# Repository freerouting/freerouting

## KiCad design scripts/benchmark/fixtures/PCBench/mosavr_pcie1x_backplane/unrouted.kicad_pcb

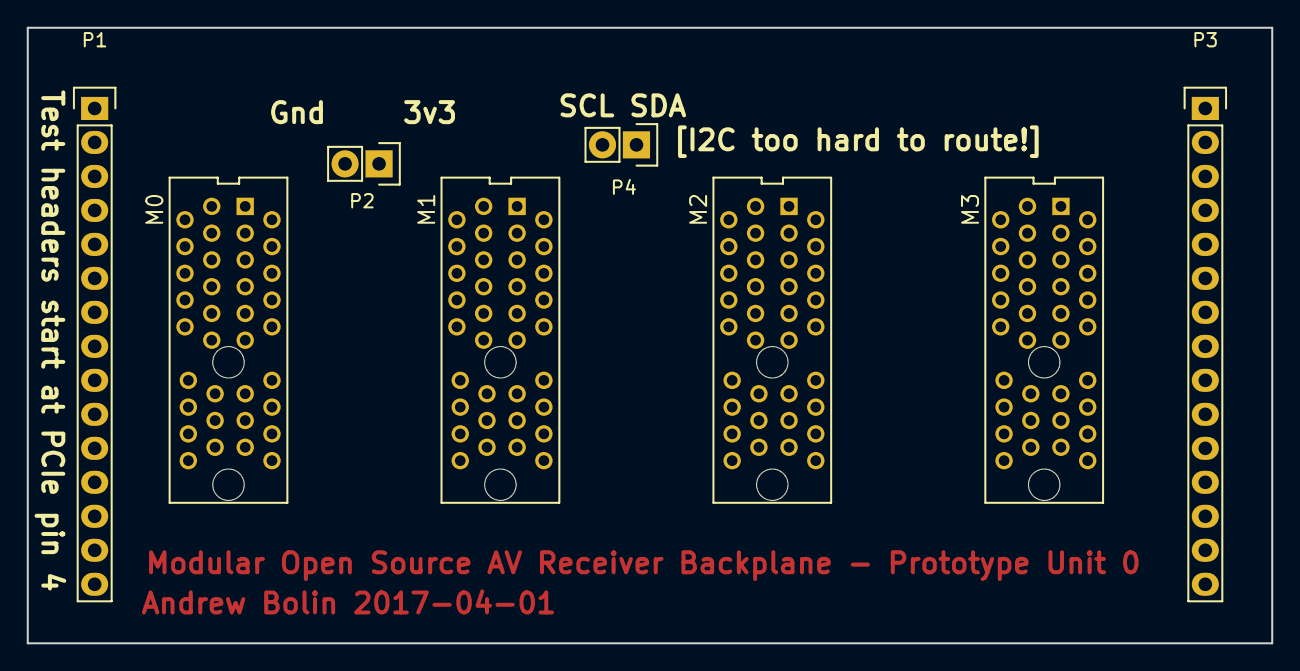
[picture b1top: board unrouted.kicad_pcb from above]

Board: 2 copper layers, 93.0 x 46.0 mm, 8 parts (0 on the bottom side), 54 nets, no tracks yet.

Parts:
M0, M1, M2, M3: pcie_1x_conn; x1socket
P1, P3: CONN_01X15; Pin_Header_Straight_1x15
P2, P4: CONN_01X02; Pin_Header_Straight_1x02

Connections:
+3V3: M0.A5, M0.A17, M0.B5, M0.B17, M1.A5, M1.A17, M1.B1, M1.B5, M1.B17, M2.A5, M2.A17, M2.B2, M2.B5, M2.B17, M3.A5, M3.A17, M3.B1, M3.B2, M3.B5, M3.B17, P1.2, P1.14, P2.1, P3.2, P3.14
/SCL: M0.B7, M1.B7, M2.B7, M3.B7, P1.4, P4.2
/SDA: M0.A7, M1.A7, M2.A7, M3.A7, P3.4, P4.1
GND: M0.A4, M0.A16, M0.B1, M0.B2, M0.B3, M0.B4, M0.B16, M1.A4, M1.A16, M1.B4, M1.B16, M2.A4, M2.A16, M2.B1, M2.B3, M2.B4, M2.B16, M3.A4, M3.A16, M3.B3, M3.B4, M3.B16, P1.1, P1.13, P2.2, P3.1, P3.13
unnamed: M0.A6, M1.B6
unnamed: M0.A8, M1.B8
unnamed: M0.A9, M1.B9
unnamed: M0.A10, M1.B10
unnamed: M0.A11, M1.B11
unnamed: M0.A12, M1.B12
unnamed: M0.A13, M1.B13
unnamed: M0.A14, M1.B14
unnamed: M0.A15, M1.B15
unnamed: M0.A18, M1.B18
unnamed: M0.B6, P1.3
unnamed: M0.B8, P1.5
unnamed: M0.B9, P1.6
unnamed: M0.B10, P1.7
unnamed: M0.B11, P1.8
unnamed: M0.B12, P1.9
unnamed: M0.B13, P1.10
unnamed: M0.B14, P1.11
unnamed: M0.B15, P1.12
unnamed: M0.B18, P1.15
unnamed: M1.A6, M2.B6
unnamed: M1.A8, M2.B8
unnamed: M1.A9, M2.B9
unnamed: M1.A10, M2.B10
unnamed: M1.A11, M2.B11
unnamed: M1.A12, M2.B12
unnamed: M1.A13, M2.B13
unnamed: M1.A14, M2.B14
unnamed: M1.A15, M2.B15
unnamed: M1.A18, M2.B18
unnamed: M2.A6, M3.B6
unnamed: M2.A8, M3.B8
unnamed: M2.A9, M3.B9
unnamed: M2.A10, M3.B10
unnamed: M2.A11, M3.B11
unnamed: M2.A12, M3.B12
unnamed: M2.A13, M3.B13
unnamed: M2.A14, M3.B14
unnamed: M2.A15, M3.B15
unnamed: M2.A18, M3.B18
unnamed: M3.A6, P3.3
unnamed: M3.A8, P3.5
unnamed: M3.A9, P3.6
unnamed: M3.A10, P3.7
unnamed: M3.A11, P3.8
unnamed: M3.A12, P3.9
unnamed: M3.A13, P3.10
unnamed: M3.A14, P3.11
unnamed: M3.A15, P3.12
unnamed: M3.A18, P3.15

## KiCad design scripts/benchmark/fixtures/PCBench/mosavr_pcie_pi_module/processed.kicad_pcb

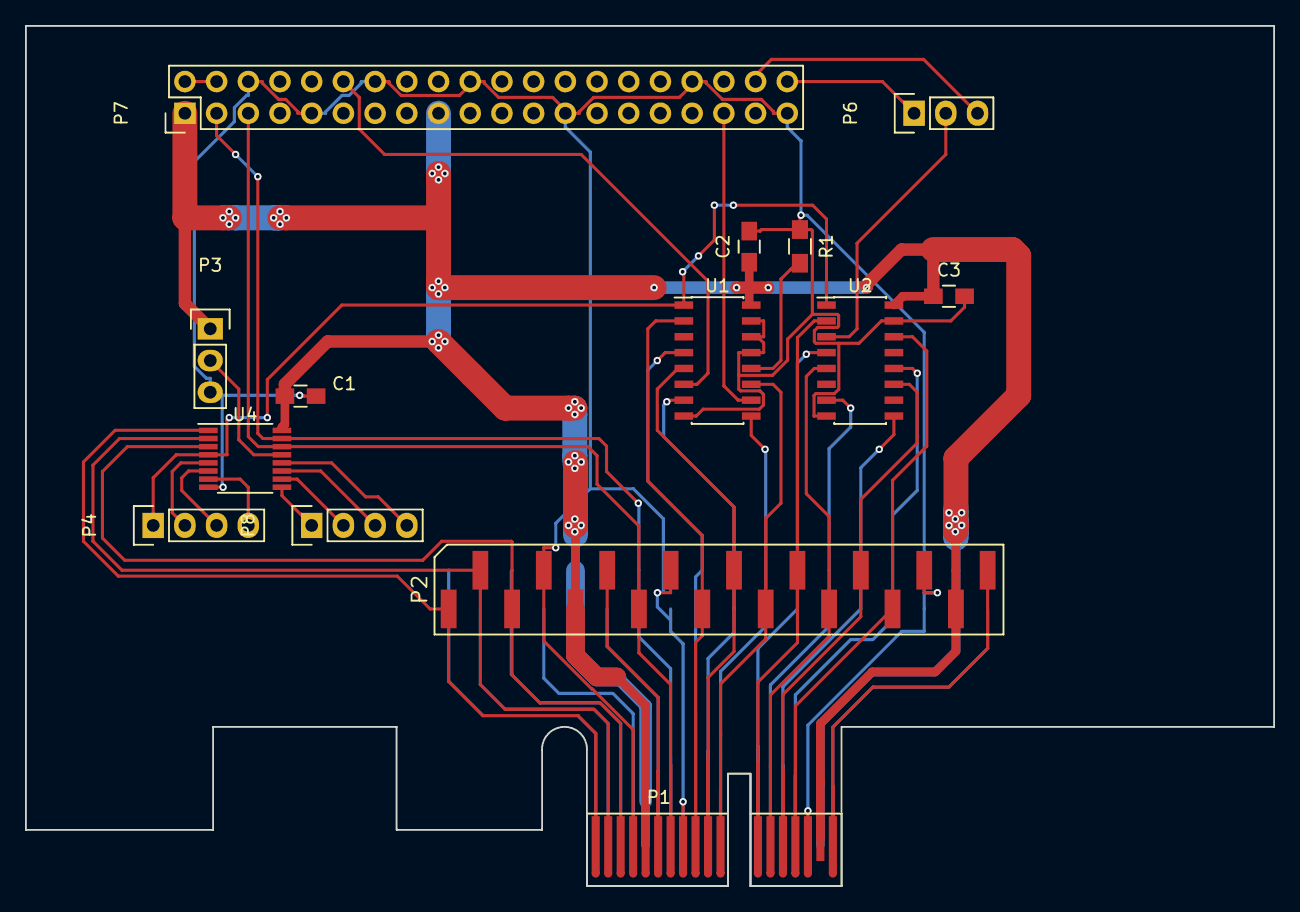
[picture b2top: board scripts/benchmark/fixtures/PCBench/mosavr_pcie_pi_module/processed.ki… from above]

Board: 2 copper layers, 100.0 x 68.9 mm, 15 parts (1 on the bottom side), 45 nets.

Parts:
C1, C2, C3: 0.1uF; C_0805_HandSoldering
P1: pcie_1x_edge; PCI-EXPRESS
P2, P5: CONN_01X18; smd_1x18_B
P3, P6: CONN_01X03; Pin_Header_Straight_1x03
P4, P8: CONN_01X04; Pin_Header_Straight_1x04
P7: CONN_02X20; Pin_Header_Straight_2x20
R1: 10k; R_0805_HandSoldering
U1, U2: 74HCT157; SOIC-16_3.9x9.9mm_Pitch1.27mm
U4: PCA9500; TSSOP-16_4.4x5mm_Pitch0.65mm

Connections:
+3V3: C1.1, C2.1, C3.1, P1.A5, P1.A17, P1.B5, P1.B17, P2.5, P2.17, P3.1, P5.5, P5.17, P7.1, P7.17, U1.16, U2.16, U4.16
+5V: P7.2, P7.4
/A0: P1.B1, P2.1, U4.1
/A1: P1.B2, P2.2, U4.2
/A2: P1.B3, P2.3, U4.3
/I2S0_in: P1.B12, P2.12, U2.2
/I2S0_mod: P6.2, U2.3
/I2S0_out: P1.A12, P5.12, U2.4
/I2S1_in: P1.B13, P2.13, U2.5
/I2S1_out: P1.A13, P5.13, U2.7
/I2S2_in: P1.B14, P2.14, U2.11
/I2S2_out: P1.A14, P5.14, U2.9
/I2S3_in: P1.B15, P2.15, U2.14
/I2S3_out: P1.A15, P5.15, U2.12
/LRclk_in: P1.B11, P2.11, U1.11
/LRclk_mod: P7.35, U1.10
/LRclk_out: P1.A11, P5.11, U1.9
/Mclk_in: P1.B9, P2.9, U1.2
/Mclk_out: P1.A9, P5.9, U1.4
/SCL: P1.B7, P2.7, P7.5, U4.14
/SDA: P1.A7, P5.7, P7.3, U4.15
/Sclk_in: P1.B10, P2.10, U1.5
/Sclk_mod: P7.12, U1.6
/Sclk_out: P1.A10, P5.10, U1.7
/pi_header/I2S_in_to_pi: P6.3, P7.38
/pi_header/I2S_out_from_pi: P6.1, P7.40
GND: C1.2, C2.2, C3.2, P1.A8, P1.A16, P1.B4, P1.B8, P1.B16, P2.4, P2.8, P2.16, P3.3, P5.8, P5.16, P7.6, P7.9, P7.14, P7.20, P7.25, P7.34, P7.39, R1.1, U1.8, U1.13, U1.14, U1.15, U2.8, U2.15, U4.8
unnamed: P1.A1, P5.1
unnamed: P1.A2, P5.2
unnamed: P1.A3, P5.3
unnamed: P1.A4, P5.4
unnamed: P1.A6, P5.6
unnamed: P1.A18, P5.18
unnamed: P1.B6, P2.6
unnamed: P1.B18, P2.18
unnamed: P3.2, U4.13
unnamed: P4.1, U1.1, U2.1, U4.4
unnamed: P4.2, U4.5
unnamed: P4.3, U4.6
unnamed: P4.4, U4.7
unnamed: P8.1, U4.9
unnamed: P8.2, U4.10
unnamed: P8.3, U4.11
unnamed: P8.4, U4.12
unnamed: R1.2, U1.12

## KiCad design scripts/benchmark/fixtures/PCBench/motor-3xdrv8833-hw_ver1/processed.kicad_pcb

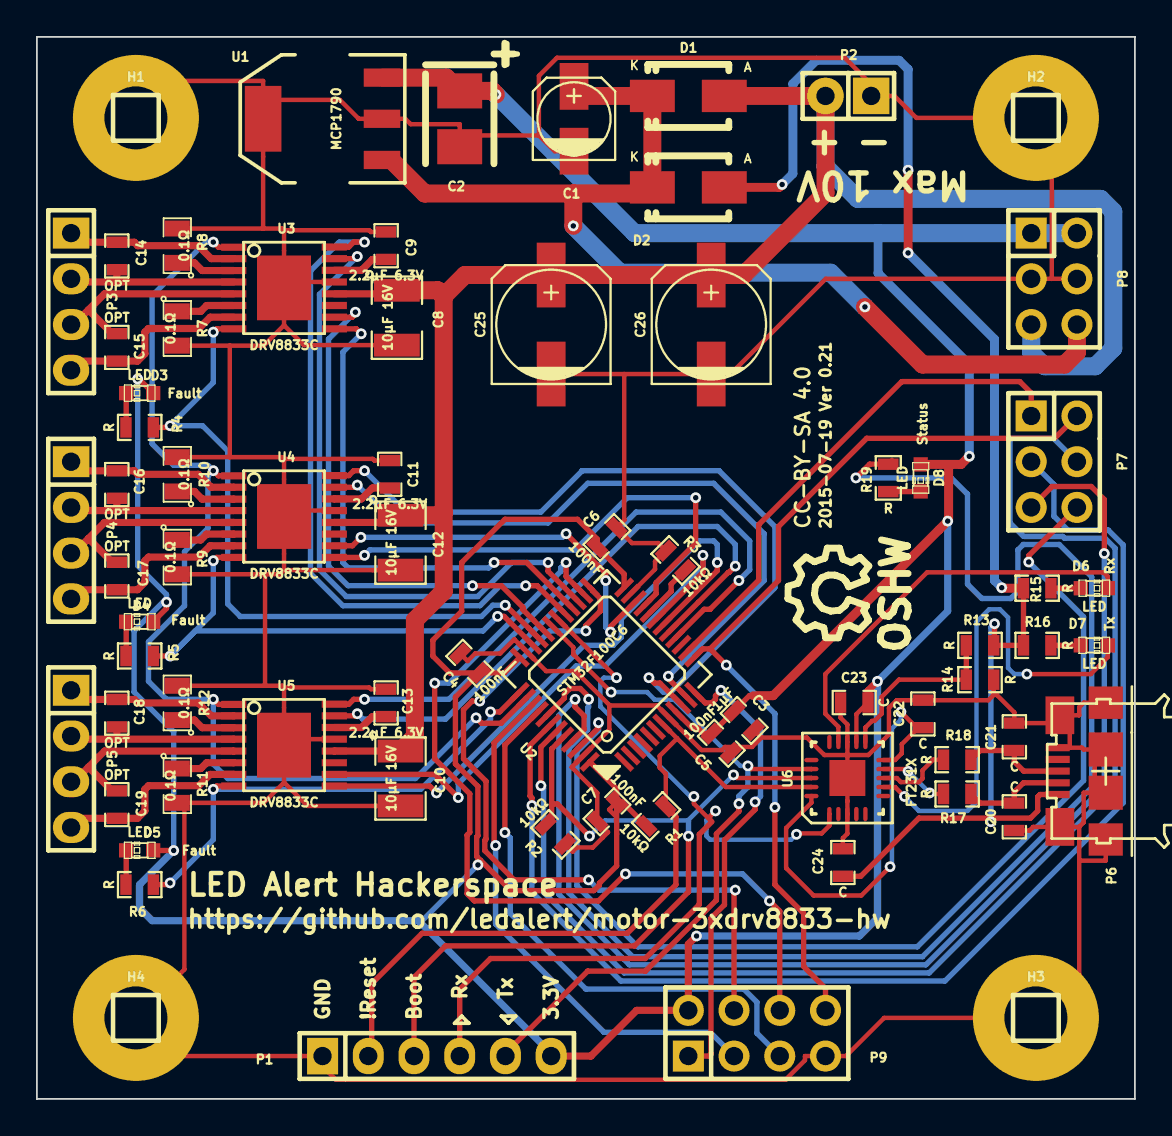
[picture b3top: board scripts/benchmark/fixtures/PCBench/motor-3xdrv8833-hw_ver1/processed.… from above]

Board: 2 copper layers, 61.0 x 59.0 mm, 73 parts (0 on the bottom side), 73 nets.

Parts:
C1: 1µF 35V; c_elec_4x5.3
C2: 1µF 6.3V; TantalC_SizeB_EIA-3528_Reflow
C3: 1µF; SMD-0603_c
C4, C5, C6, C7: 100nF; SMD-0603_c
C8, C10, C12: 10µF 16V; SMD-1210
C9, C11, C13: 2.2µF 6.3V; SMD-0603_c
C14, C15, C16, C17, C18, C19: OPT; SMD-0603_c
C20, C21, C22, C23, C24: C; SMD-0603_c
C25, C26: 220µF 16V; c_elec_6.3x7.7
D1, D2: DIODESCH; Diode-SMA_Standard
D3, D4, D5, D6, D7, D8: LED; LED-0603
H1, H2, H3, H4: CONN_1; Pin_Header_Straight_1x01
P1: CONN_6; Pin_Header_Straight_1x06
P2: CONN_2; Pin_Header_Straight_1x02
P3, P4, P5: CONN_4; Pin_Header_Straight_1x04
P6: USB_Micro_B; USB MICRO B
P7, P8: CONN_3X2; Pin_Header_Straight_2x03
P9: CONN_4X2; Pin_Header_Straight_2x04
R1, R2, R3: 10kΩ; SMD-0603_r
R4, R5, R6, R13, R14, R15, R16, R17, R18, R19: R; SMD-0603_r
R7, R8, R9, R10, R11, R12: 0.1Ω; SMD-0805
SYM: Symbol_OSHW-Logo_SilkScreen_07Jul2012; Symbol_OSHW-Logo_SilkScreen
U1: MCP1790; SOT-223
U2: STM32F100C6; lqfp-48
U3, U4, U5: DRV8833C; SSOP-16(EP)
U6: FT231X; QFN_20-1EP

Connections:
/BOOT1: R3.1, U2.20
/ESP8266 PTH Connector/CH_PD: P9.6, U2.26
/ESP8266 PTH Connector/GPIO0: P9.3, U2.39
/ESP8266 PTH Connector/GPIO2: P9.5, U2.40
/ESP8266 PTH Connector/RST: P9.4, U2.25
/ESP8266 PTH Connector/RXD: P9.1, U2.12
/ESP8266 PTH Connector/TXD: P7.2, P9.8, U2.13
/GPIO1: P7.1, U2.14
/GPIO5: P7.3, U2.42
/GPIO6: P7.4, U2.43
/GPIO7: P7.5, U2.45
/GPIO8: P7.6, U2.46
/PC Interface/DTR: P1.3, R2.1, U2.44, U6.18
/PC Interface/RTS: P1.2, R1.2, U2.7, U6.19
/PC Interface/RX: P1.4, U2.30, U6.1
/PC Interface/TX: P1.5, U2.31, U6.17
/PC Interface/VBUS: C24.1, D2.1, P6.1, R13.2, R15.2, R16.2
/STATUS_LED: R19.2, U2.41
/VDD_INT: C1.1, D1.2, D2.2, P8.6, U1.1
/drv8833_1/AIN1: U2.29, U3.16
/drv8833_1/AIN2: U2.27, U3.15
/drv8833_1/AOUT1: C14.2, P3.1, U3.2
/drv8833_1/AOUT2: C14.1, P3.2, U3.4
/drv8833_1/BIN1: U2.28, U3.9
/drv8833_1/BIN2: U2.32, U3.10
/drv8833_1/BOUT1: C15.2, P3.4, U3.7
/drv8833_1/BOUT2: C15.1, P3.3, U3.5
/drv8833_1/FAULT_OUT: R4.2, U2.33, U3.8
/drv8833_1/SLEEP_IN: U2.38, U3.1, U4.1, U5.1
/drv8833_2/AIN1: U2.10, U4.16
/drv8833_2/AIN2: U2.11, U4.15
/drv8833_2/AOUT1: C16.2, P4.1, U4.2
/drv8833_2/AOUT2: C16.1, P4.2, U4.4
/drv8833_2/BIN1: U2.21, U4.9
/drv8833_2/BIN2: U2.22, U4.10
/drv8833_2/BOUT1: C17.2, P4.4, U4.7
/drv8833_2/BOUT2: C17.1, P4.3, U4.5
/drv8833_2/FAULT_OUT: R5.2, U2.34, U4.8
/drv8833_3/AIN1: U2.16, U5.16
/drv8833_3/AIN2: U2.17, U5.15
/drv8833_3/AOUT1: C18.2, P5.1, U5.2
/drv8833_3/AOUT2: C18.1, P5.2, U5.4
/drv8833_3/BIN1: U2.18, U5.9
/drv8833_3/BIN2: U2.19, U5.10
/drv8833_3/BOUT1: C19.2, P5.4, U5.7
/drv8833_3/BOUT2: C19.1, P5.3, U5.5
/drv8833_3/FAULT_OUT: R6.2, U2.37, U5.8
GND: C1.2, C2.2, C3.2, C4.2, C5.2, C6.2, C7.2, C8.2, C9.2, C10.2, C11.2, C12.2, C13.2, C20.2, C21.2, C22.2, C23.2, C24.2, C25.2, C26.2, H1.1, H2.1, H3.1, H4.1, P1.1, P2.1, P6.5, P6.S, P8.3, P8.4, P9.7, R2.2, R3.2, R7.2, R8.2, R9.2, R10.2, R11.2, R12.2, R14.1, U1.2, U1.4, U2.8, U2.23, U2.35, U2.47, U3.13, U3.17, U4.13, U4.17, U5.13, U5.17, U6.3, U6.13, U6.21
unnamed: C9.1, U3.14
unnamed: C11.1, U4.14
unnamed: C13.1, U5.14
unnamed: C20.1, P6.2, R17.2
unnamed: C21.1, P6.3, R18.2
unnamed: C22.1, U6.10, U6.20
unnamed: D3.2, R4.1
unnamed: D4.2, R5.1
unnamed: D5.2, R6.1
unnamed: D6.1, R15.1
unnamed: D6.2, U6.14
unnamed: D7.1, R16.1
unnamed: D7.2, U6.7
unnamed: D8.2, R19.1
unnamed: R7.1, U3.6
unnamed: R8.1, U3.3
unnamed: R9.1, U4.6
unnamed: R10.1, U4.3
unnamed: R11.1, U5.6
unnamed: R12.1, U5.3
unnamed: R13.1, R14.2, U6.11
unnamed: R17.1, U6.9
unnamed: R18.1, U6.8
VCC: C2.1, C3.1, C4.1, C5.1, C6.1, C7.1, C23.1, D3.1, D4.1, D5.1, D8.1, P1.6, P8.1, P8.2, P9.2, R1.1, U1.3, U2.9, U2.24, U2.36, U2.48, U6.12
VDD: C8.1, C10.1, C12.1, C25.1, C26.1, D1.1, P2.2, P8.5, U3.12, U4.12, U5.12

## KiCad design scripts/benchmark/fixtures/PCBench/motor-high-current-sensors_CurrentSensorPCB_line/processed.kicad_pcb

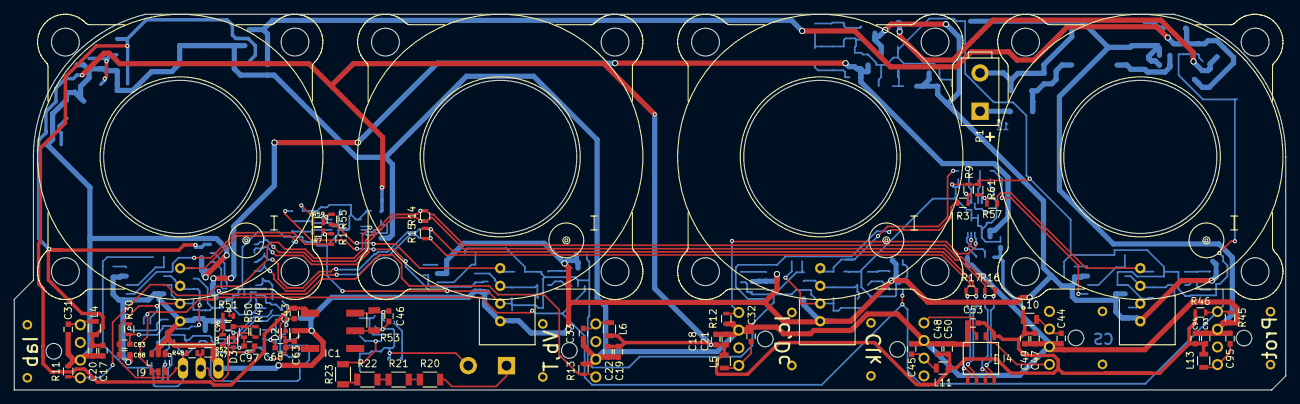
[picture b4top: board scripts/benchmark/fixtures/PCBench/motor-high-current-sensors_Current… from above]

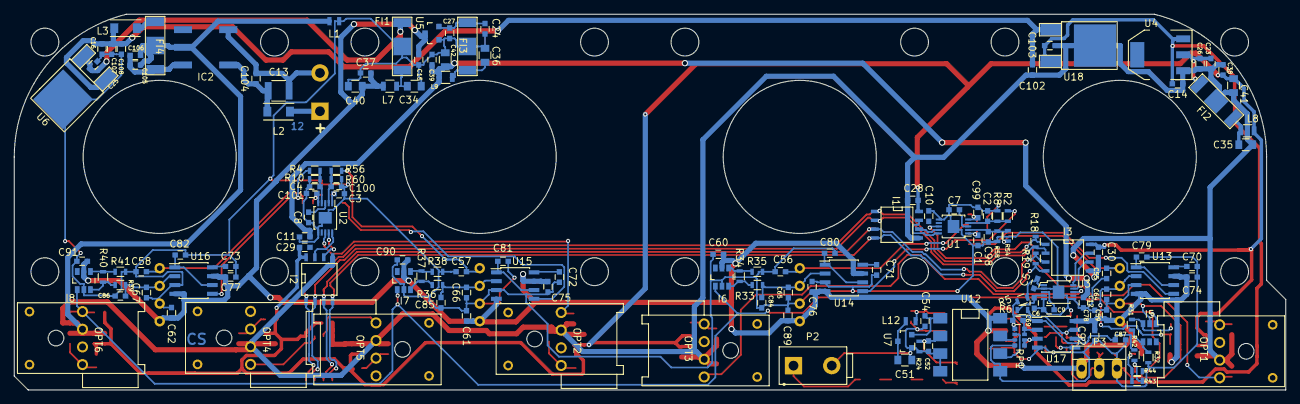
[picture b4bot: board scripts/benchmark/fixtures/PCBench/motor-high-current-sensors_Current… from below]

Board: 2 copper layers, 182.8 x 54.0 mm, 222 parts (150 on the bottom side), 102 nets.

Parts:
C1, C2, C3, C4, C5, C6, C98, C99, C100, C101: 5.1n; C_0603
C7, C8, C9, C10, C11, C12, C20, C21, C22, C31, C32, C33, C44, C45, C47, C48, C94, C95: 10u; C_0603
C13: 22u, 16V; C_1210
C14, C15, C16, C17, C18, C19, C28, C29, C30, C43, C49, C50, C53, C74, C75, C76, C77, C79, C80, C81, C82, C88, C89, C90, C91, C92, C93, C102: 100n; C_0603
C23, C24, C25, C54, C103, C105, C107: 1u; C_0603
C26, C27, C46, C68, C69, C104, C106, C108: 1n; C_0603
C34, C35, C36: 10u, 6.3v; C_0805
C37, C38, C39, C52: 10n; C_0603
C40, C41, C42, C51: 4u7; C_0805
C55, C56, C57, C58, C59, C60, C61, C62, C63, C78, C83, C84, C85, C86, C87, C96, C97: 47n; C_0603
C64, C65, C66, C67: 4n7; C_0603
C70, C71, C72, C73: 27p; C_0603
D2, D3: 3.3V; SOD-523
FI1, FI2, FI3, FI4: NFE61P; EMI_Filter_murata
I1, I2, I3: DS90LV028A; SOIC-8-N
I4: DS90LV027A; SOIC-8-N
I5, I6, I7, I8, I9: ADCMP671; TSOT-6-MK06A
IC1, IC2: Murata_MTU1; MTU1_Murata_DCDC
L1: INDUCTOR_SMALL; Neosid_Inductor_SM0603CG
L2, L3: 10uH; Neosid_Inductor_SM1206
L4, L5, L6, L10, L11, L13: 1uH; R_0805
L7, L8, L9: ?; R_0805
L12: 10uH; Neosid_Inductor_SM0603CG
OPT1, OPT2, OPT3, OPT6: AFBR-1634Z; HFBR-xx3xZ
OPT4, OPT5: AFBR-26x; HFBR-xx3xZ
P1, P2: CONN_01X02; Connector_Header_2Way_39-29-3026
P3: CONN_01X03; PINHEAD1-3
R1, R2, R3, R4, R54, R55, R56, R57: 3.6k; R_0603
R5, R6: 51; R_0603
R7, R8, R9, R10, R58, R59, R60, R61: 6.8k; R_0603
R11, R12, R13, R46: 4k7; R_0603
R14, R15, R16, R17, R18, R19: 330; R_0603
R20, R21, R22, R23: 100k; R_1206
R24: 158; R_0603
R30, R33, R36, R39: 1k6; R_0603
R31, R34, R37, R40: 910; R_0603
R32, R35, R38, R41: 270; R_0603
R42, R43, R44, R45, R47, R48, R49, R50, R51: DNP; R_0603
R52: 0R; R_0603
R53: 270; R_1206
RP1: R_PACK4; ACAS0612
U1, U2: LTC1407-1; MSOP-10-1EP_3x3mm_Pitch0.5mm
U3: LTC1407; MSOP-10-1EP_3x3mm_Pitch0.5mm
U4: LD1117S33TR; SOT-223
U5: MCP1700T-330; SOT-23
U6, U18: MC78M05CDT; TO-252-2Lead
U7: MCP1700T-500; SOT-23
U8, U9, U10: HTFS800; HTFS-Series_LEM-HallEffektCurrentTransducer
U11: HTFS400; HTFS-Series_LEM-HallEffektCurrentTransducer
U12: ACPL-C870; DIP-8_SMD
U13, U14, U15, U16: MAX7480; SOIC-8_3.9x4.9mm_Pitch1.27mm
U17: OPA350; SOIC-8_3.9x4.9mm_Pitch1.27mm

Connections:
+3.3VADC: C11.2, C12.2, C39.1, C42.1, L9.2
+3V3: C17.2, C18.2, C19.2, C20.2, C21.2, C22.2, C28.2, C29.2, C30.2, C38.1, C41.1, C47.2, C48.2, C49.2, C50.2, C53.2, C93.2, C94.2, I1.8, I2.8, I3.8, I4.1, L4.1, L5.1, L6.1, L8.2, L10.1, L11.1, L13.1, R46.1
+5V: C14.1, C43.1, C103.1, IC1.1, U4.3, U18.3
+5VA: C15.1, C37.1, C40.1, C59.2, C60.2, C61.2, C62.2, C63.2, C74.1, C75.1, C76.1, C77.1, C78.1, C88.2, C89.2, C90.2, C91.2, C92.2, I6.5, I7.5, I8.5, I9.5, L7.2, P3.1, R47.2, U5.3, U8.1, U9.1, U10.1, U11.1, U12.8, U13.4, U13.7, U14.4, U14.7, U15.4, U15.7, U16.4, U16.7, U17.8
+9V: C16.1, C102.1, C107.1, C108.1, L3.2, U6.1, U18.1
/ADC_Ck+: I1.3, I2.3, I3.3, I4.6, R15.2, R17.2, R19.2
/ADC_Ck-: I1.4, I2.4, I3.4, I4.5, R15.1, R17.1, R19.1
/ADC_Smp+: I1.2, I2.2, I3.2, I4.7, R14.1, R16.1, R18.1
/ADC_Smp-: I1.1, I2.1, I3.1, I4.8, R14.2, R16.2, R18.2
/I_U: R1.2, U13.5
/I_V: R2.2, U14.5
/I_W: R3.2, U15.5
/I_bus: R4.2, U16.5
/I_bus_sense: C67.1, C86.1, R39.2, U11.3, U16.2
/I_u_sense: C64.1, C83.1, R30.2, U8.3, U13.2
/I_v_sense: C65.1, C84.1, R33.2, U9.3, U14.2
/I_w_sense: C66.1, C85.1, R36.2, U10.3, U15.2
/Over_IV_prot: I5.1, I6.1, I7.1, I8.1, I9.1, OPT6.4, R45.2, R46.2
/T_coolant: D3.1, R6.2, R52.1, U17.7
/V_bus: C69.2, C87.1, D2.1, R5.2, R42.2, RP1.4, U17.1
/V_ref_U: C55.1, R54.1, U8.4
/V_ref_V: C56.1, R55.2, U9.4
/V_ref_W: C57.1, R56.1, U10.4
/V_ref_bus: C58.1, R57.2, U11.4
AGND: C1.1, C2.1, C3.1, C4.1, C5.1, C6.1, C7.2, C8.2, C9.2, C10.1, C11.1, C12.1, C15.2, C16.2, C24.2, C25.2, C27.2, C34.2, C36.2, C37.2, C39.2, C40.2, C42.2, C43.2, C55.2, C56.2, C57.2, C58.2, C59.1, C60.1, C61.1, C62.1, C63.1, C64.2, C65.2, C66.2, C67.2, C68.2, C70.2, C71.2, C72.2, C73.2, C74.2, C75.2, C76.2, C77.2, C78.2, C79.2, C80.2, C81.2, C82.2, C83.2, C84.2, C85.2, C86.2, C87.2, C88.1, C89.1, C90.1, C91.1, C92.1, C97.2, C98.2, C99.2, C100.2, C101.2, C107.2, C108.2, D2.2, D3.2, FI1.2, FI3.2, I5.2, I6.2, I7.2, I8.2, I9.2, IC1.3, L1.2, P3.3, R7.1, R8.1, R9.1, R10.1, R32.1, R35.1, R38.1, R41.1, R44.1, R48.1, R51.1, R58.1, R59.1, R60.1, R61.1, RP1.1, U1.6, U1.11, U2.6, U2.11, U3.2, U3.5, U3.6, U3.11, U5.1, U6.2, U8.2, U9.2, U10.2, U11.2, U12.5, U13.3, U14.3, U15.3, U16.3, U17.4
DGND: C14.2, C17.1, C18.1, C19.1, C20.1, C21.1, C22.1, C23.2, C26.2, C28.1, C30.1, C31.1, C32.1, C33.1, C35.2, C38.2, C41.2, C44.1, C45.1, C47.1, C48.1, C49.1, C50.1, C53.1, C93.1, C94.1, C95.1, C102.2, C103.2, C105.2, C106.2, FI2.2, FI4.2, I1.5, I2.5, I3.5, I4.4, IC2.5, L1.1, OPT1.3, OPT2.3, OPT3.3, OPT4.2, OPT5.2, OPT6.3, R11.1, R12.1, R13.1, R45.1, U4.1, U18.2
unnamed: C1.2, R1.1, R7.2, U1.1
unnamed: C2.2, R2.1, R8.2, U1.4
unnamed: C3.2, R3.1, R9.2, U2.1
unnamed: C4.2, R4.1, R10.2, U2.4
unnamed: C5.2, R5.1, U3.1
unnamed: C6.2, R6.1, U3.4
unnamed: C7.1, U1.3
unnamed: C8.1, U2.3
unnamed: C9.1, U3.3
unnamed: C23.1, C26.1, FI2.1, U4.2
unnamed: C24.1, C27.1, FI3.1, U5.2
unnamed: C25.1, FI1.1, U6.3
unnamed: C31.2, L4.2, OPT1.1
unnamed: C32.2, L5.2, OPT2.1
unnamed: C33.2, L6.2, OPT3.1
unnamed: C34.1, FI1.3, L7.1
unnamed: C35.1, FI2.3, L8.1
unnamed: C36.1, FI3.3, L9.1
unnamed: C44.2, L10.2, OPT4.3
unnamed: C45.2, L11.2, OPT5.3
unnamed: C46.1, C51.2, C52.2, C54.2, IC1.5, P2.2, R24.2, R53.1, U7.1, U12.3, U12.4
unnamed: C46.2, IC1.6, L12.1, R53.2
unnamed: C51.1, L12.2, U7.3
unnamed: C52.1, R23.1, R24.1, U12.2
unnamed: C54.1, U7.2, U12.1
unnamed: C68.1, RP1.7, RP1.8, U17.3
unnamed: C69.1, RP1.5, RP1.6, U17.2
unnamed: C70.1, U13.8
unnamed: C71.1, U14.8
unnamed: C72.1, U15.8
unnamed: C73.1, U16.8
unnamed: C79.1, U13.1, U13.6
unnamed: C80.1, U14.1, U14.6
unnamed: C81.1, U15.1, U15.6
unnamed: C82.1, U16.1, U16.6
unnamed: C95.2, L13.2, OPT6.1
unnamed: C96.1, R51.2, R52.2, U17.6
unnamed: C96.2, R49.1, R50.2
unnamed: C97.1, R50.1, U17.5
unnamed: C98.1, R54.2, R58.2, U1.2
unnamed: C99.1, R55.1, R59.2, U1.5
unnamed: C100.1, R56.2, R60.2, U2.2
unnamed: C101.1, R57.1, R61.2, U2.5
unnamed: C13.2, C104.1, IC2.3, P1.2
unnamed: C13.1, C104.2, IC2.1, L2.2
unnamed: C105.1, C106.1, FI4.1, IC2.6
unnamed: FI4.3, L3.1
unnamed: I1.6, U1.9
unnamed: I1.7, U1.10
unnamed: I2.6, U2.9
unnamed: I2.7, U2.10
unnamed: I3.6, U3.9
unnamed: I3.7, U3.10
unnamed: I4.2, OPT4.1
unnamed: I4.3, OPT5.1
unnamed: I5.3, R30.1, R31.2
unnamed: I5.4, R31.1, R32.2
unnamed: I6.3, R33.1, R34.2
unnamed: I6.4, R34.1, R35.2
unnamed: I7.3, R36.1, R37.2
unnamed: I7.4, R37.1, R38.2
unnamed: I8.3, R39.1, R40.2
unnamed: I8.4, R40.1, R41.2
unnamed: I9.3, R42.1, R43.2
unnamed: I9.4, R43.1, R44.2
unnamed: L2.1, P1.1
unnamed: OPT1.4, R11.2, U1.8
unnamed: OPT2.4, R12.2, U2.8
unnamed: OPT3.4, R13.2, U3.8
unnamed: P2.1, R20.2
unnamed: P3.2, R47.1, R48.2, R49.2
unnamed: R20.1, R21.2
unnamed: R21.1, R22.2
unnamed: R22.1, R23.2
unnamed: RP1.2, U12.7
unnamed: RP1.3, U12.6

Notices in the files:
scripts/benchmark/fixtures/PCBench/motor-3xdrv8833-hw_ver1/processed.kicad_pcb:
CC-BY-SA 4.0
